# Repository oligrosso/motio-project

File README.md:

# 🧠 MOTIO — Biomedical Instrumentation Project

**MOTIO** is an end-to-end **biomedical instrumentation system** designed for the **analysis and treatment support of Parkinson’s Disease**, providing a **non-invasive, portable, and objective** approach to motor symptom monitoring.

The project integrates **wearable hardware**, **embedded firmware**, and an **intelligent analysis platform**, enabling both clinical and ambulatory use.

> 🩺 *Making motion science accessible.*

---

## 🎯 Project Objective

The main goal of MOTIO is to develop and validate a system capable of:

- 🧤 Delivering **vibrotactile therapeutic stimulation**
- 📟 Objectively measuring motor symptoms, especially tremor
- 📊 Processing and visualizing motion data through a clinical interface
- 📈 Complementing (not replacing) traditional clinical assessments (e.g. MDS-UPDRS)

---

## 🧩 System Architecture Overview

### 📁 Repository Structure

- 🧤 **MotioGlove/** — Wearable vibrotactile therapeutic device  
- 📟 **MotioSensor/** — Portable inertial measurement device (IMU)  
- 📊 **MotioMetrics/** — Motion analysis and visualization platform  

Each module can operate independently, but together they form a **complete ecosystem** for treatment, measurement, and analysis.

---

## 🧤 MotioGlove — Vibrotactile Therapeutic Glove

Wearable glove designed to apply **Vibrotactile Coordinated Reset (vCR)** stimulation to the fingertips.

### 🔬 Scientific Background
Based on research by **Tass et al. (Stanford University)**, vCR aims to **desynchronize pathological neural networks** using controlled mechanical stimulation.

### ⚙️ Key Features
- Vibrotactile stimulation at **250 Hz**
- Alternating stimulation of **finger pairs**
- Randomized stimulation sequences (**Fisher–Yates algorithm**)
- Temporal pauses with **jitter**
- Autonomous **2-hour therapy sessions**
- Button-based control and LED feedback

### ✅ Advantages
- Non-invasive
- Portable
- Ambulatory use
- High patient comfort
- No reported side effects

---

## 📟 MotioSensor — Inertial Measurement Device

Portable sensing unit designed to objectively capture motion data with **clinical-grade precision**.

### 🧠 Measured Signals
- 3-axis acceleration
- 3-axis angular velocity
- Orientation estimation (Yaw, Pitch, Roll)

### 🔄 Operating Modes
- 🏥 **Clinical mode**: real-time WiFi transmission
- 🏠 **Ambulatory mode**: local storage on microSD card

### 📁 Output
- `.csv` files containing:
  - Raw sensor signals
  - Timestamped activity annotations

---

## 📊 MotioMetrics — Motion Analysis Platform

Software platform responsible for **data processing, analysis, and visualization**.

### 🧠 Backend (Python)
- CSV file ingestion
- Automatic signal processing
- Tremor episode detection
- Computation of:
  - Dominant frequency
  - RMS amplitude
  - Episode duration
- Spectral analysis (FFT + **Burg method**)

### 🖥️ Web Interface
- Clinical-oriented UI
- Manual CSV upload
- Interactive visualizations (Plotly.js)
- Patient data registration
- PDF report export
- Local measurement history

### 🔴 Real-Time Analysis
- **WebSocket-based** communication
- Live signal visualization
- Activity logging with timestamps
- Automatic download of recorded data at session end

---

## 🔁 System Workflow

### 🧪 Real-Time Analysis
```mermaid
flowchart LR
  A[MotioSensor] -->|WiFi / WebSockets| B[MotioMetrics backend]
  B --> C[Live processing]
  C --> D[Web interface]
  D --> E[Live visualization]
```

### 📂 Offline CSV Analysis

```mermaid
flowchart LR
  A[MotioSensor<br/>CSV files] --> B[MotioMetrics]
  B --> C[Signal processing]
  C --> D[Metrics extraction]
  D --> E[Reports and visualizations]
```
## 🧪 Validation & Results

The system was evaluated on:
- Parkinson’s patients with tremor
- Parkinson’s patients without tremor (dyskinesia)
- Control subjects

Results demonstrated:
- Strong correlation with clinical evaluation
- Robust tremor episode detection
- High usability and acceptance by patients and clinicians

---

## 🛠️ Technologies Used

- **Python** (signal processing & backend)
- **Flask + Socket.IO**
- **JavaScript / HTML / CSS**
- **Plotly.js**
- **ESP8266 (Wemos D1 Mini)**
- **MPU6050 IMU**
- **Render + GitHub**

---

## 👩‍🔬 Team

Developed as part of  
**Biomedical Instrumentation II — ITBA**

**Group 1**
- Alexa Sessarego Aurich
- Jazmín Azul Fermani  
- Olivia Grosso  
---

## ⚠️ Disclaimer

This project was developed for **academic and research purposes only**.  
It is **not a certified medical device** for commercial clinical use.

## 🗂️ Module Interaction Diagram
```mermaid
flowchart LR

  subgraph Wearables
    G[MotioGlove<br/>Vibrotactile therapy]
    P[Patient]
    S[MotioSensor<br/>IMU data acquisition]
    G -->|Therapy| P -->|Motion| S
  end

  subgraph Software
    B[MotioMetrics backend]
    W[Web interface]
    D[Desktop application]
    B --> W
    B --> D
  end

  S -->|Motion data| B

```

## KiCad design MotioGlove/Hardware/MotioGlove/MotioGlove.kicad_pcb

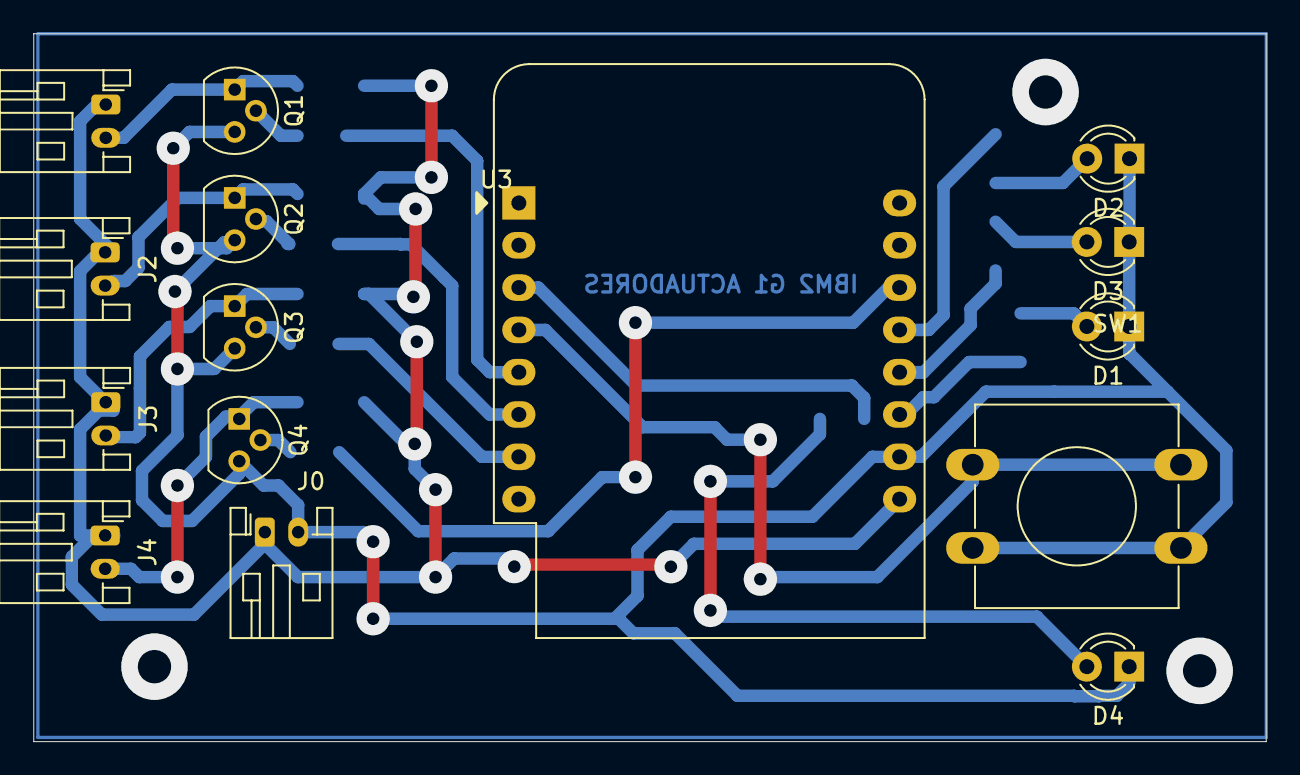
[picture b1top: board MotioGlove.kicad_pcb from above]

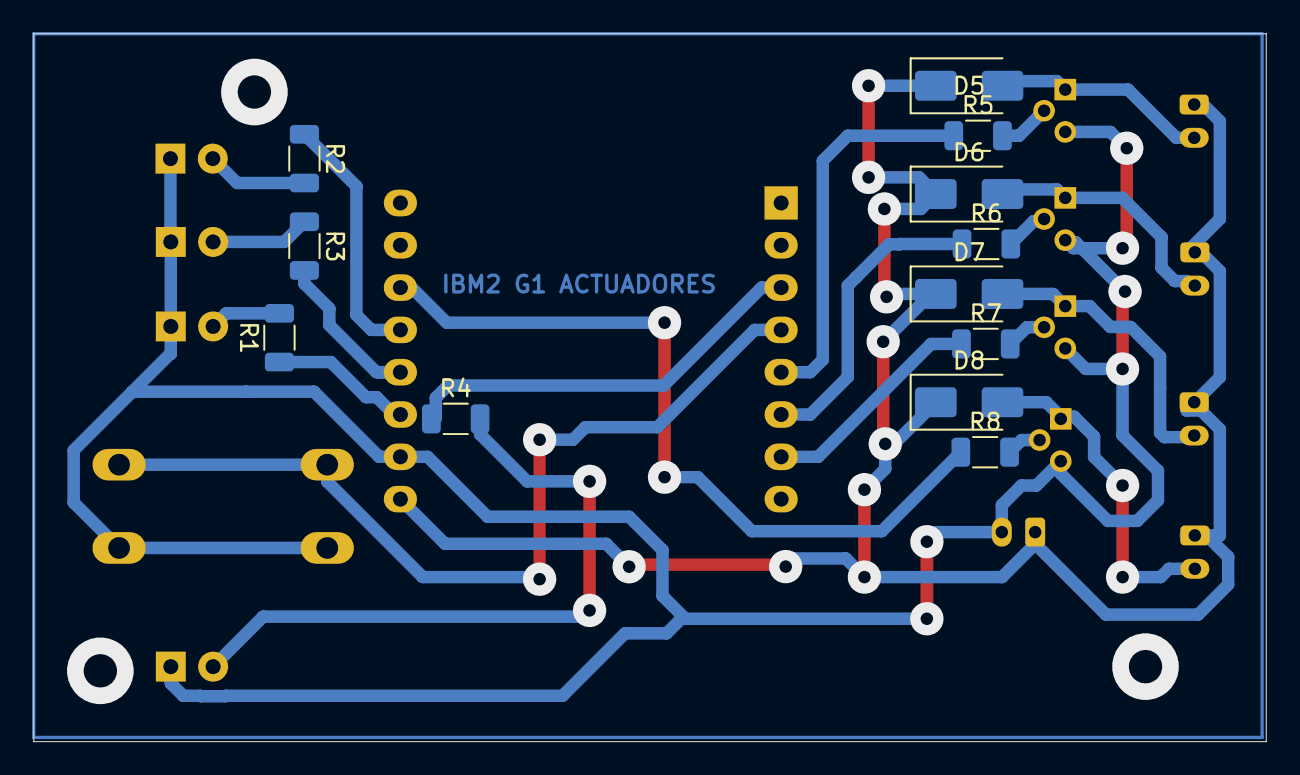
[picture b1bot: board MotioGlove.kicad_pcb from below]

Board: 2 copper layers, 74.0 x 42.5 mm, 27 parts (12 on the bottom side), 23 nets.

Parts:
D1, D2, D3: LED; LED_D3.0mm
D4: LED_STATUS; LED_D3.0mm
D5, D6, D7, D8: D; D_SMA
J0: 5V; JST_PH_S2B-PH-K_1x02_P2.00mm_Horizontal
J1, J2, J3, J4: Conn_01x02; JST_PH_S2B-PH-K_1x02_P2.00mm_Horizontal
Q1, Q2, Q3, Q4: BC547; TO-92
R1, R2, R3, R4, R5, R6, R7, R8: R; R_1206_3216Metric
SW1: SW_Push; SW_PUSH-12mm
U3: WEMOS_D1_mini; WEMOS_D1_mini_light

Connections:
/5V: D5.1 (K), D6.1 (K), D7.1 (K), D8.1 (K), J0.1, J1.1, J2.1, J3.1, J4.1, U3.9 (5V)
/D0: R4.1, U3.3 (D0)
/D1: R8.1, U3.14 (SCL/D1)
/D2: R2.1, U3.13 (SDA/D2)
/D3: R3.2, U3.12 (D3)
/D4: R1.1, U3.11 (D4)
/D5: SW1.1, U3.4 (SCK/D5)
/D6: R5.1, U3.5 (MISO/D6)
/D7: R6.1, U3.6 (MOSI/D7)
/D8: R7.1, U3.7 (CS/D8)
/GND: D1.1 (K), D2.1 (K), D3.1 (K), D4.1 (K), J0.2, Q1.3 (E), Q2.3 (E), Q3.3 (E), Q4.3 (E), SW1.2, U3.10 (GND)
unnamed: D1.2 (A), R1.2
unnamed: D2.2 (A), R2.2
unnamed: D3.2 (A), R3.1
unnamed: D4.2 (A), R4.2
unnamed: D5.2 (A), J1.2, Q1.1 (C)
unnamed: D6.2 (A), J2.2, Q2.1 (C)
unnamed: D7.2 (A), J3.2, Q3.1 (C)
unnamed: D8.2 (A), J4.2, Q4.1 (C)
unnamed: Q1.2 (B), R5.2
unnamed: Q2.2 (B), R6.2
unnamed: Q3.2 (B), R7.2
unnamed: Q4.2 (B), R8.2

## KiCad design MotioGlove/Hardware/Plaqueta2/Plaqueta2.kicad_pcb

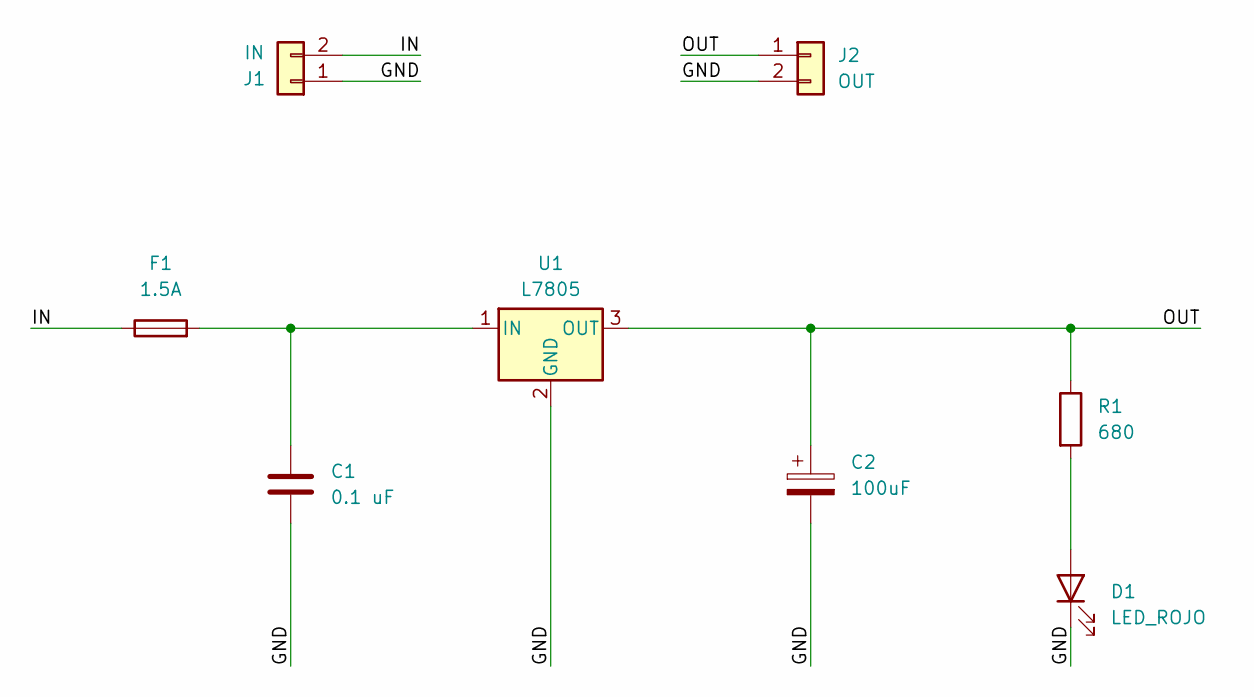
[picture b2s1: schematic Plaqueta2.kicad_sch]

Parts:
C1: 0.1 uF; C_Disc_D5.0mm_W2.5mm_P2.50mm
C2: 100uF; CP_Radial_D5.0mm_P2.50mm
D1: LED_ROJO; LED_0805_2012Metric
F1: 1.5A; Fuseholder_Cylinder-5x20mm_Schurter_0031_8201_Horizontal_Op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
J1: IN; PinHeader_1x02_P2.54mm_Vertical
J2: OUT; PinHeader_1x02_P2.54mm_Vertical
R1: 680; R_1206_3216Metric
U1: L7805; TO-252-2

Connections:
/GND: C1.2, C2.2, D1.1 (K), J1.1, J2.2, U1.2 (GND)
/IN: F1.1, J1.2
/OUT: C2.1, J2.1, R1.1, U1.3 (OUT)
unnamed: D1.2 (A), R1.2
unnamed: C1.1, F1.2, U1.1 (IN)

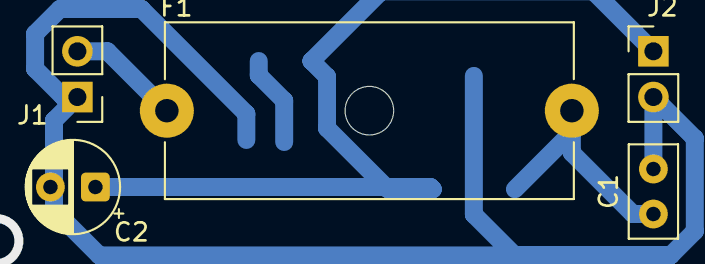
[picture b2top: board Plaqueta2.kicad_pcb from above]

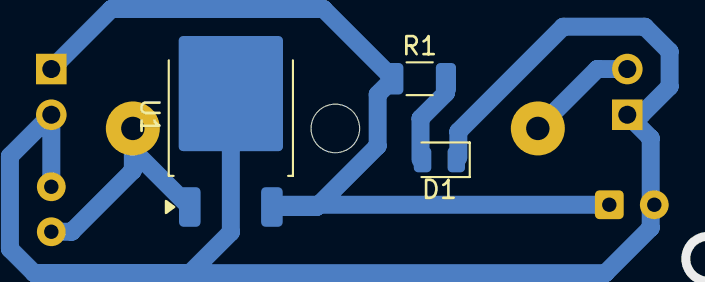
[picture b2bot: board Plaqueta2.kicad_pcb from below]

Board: 2 copper layers, 8 parts (3 on the bottom side), 5 nets.

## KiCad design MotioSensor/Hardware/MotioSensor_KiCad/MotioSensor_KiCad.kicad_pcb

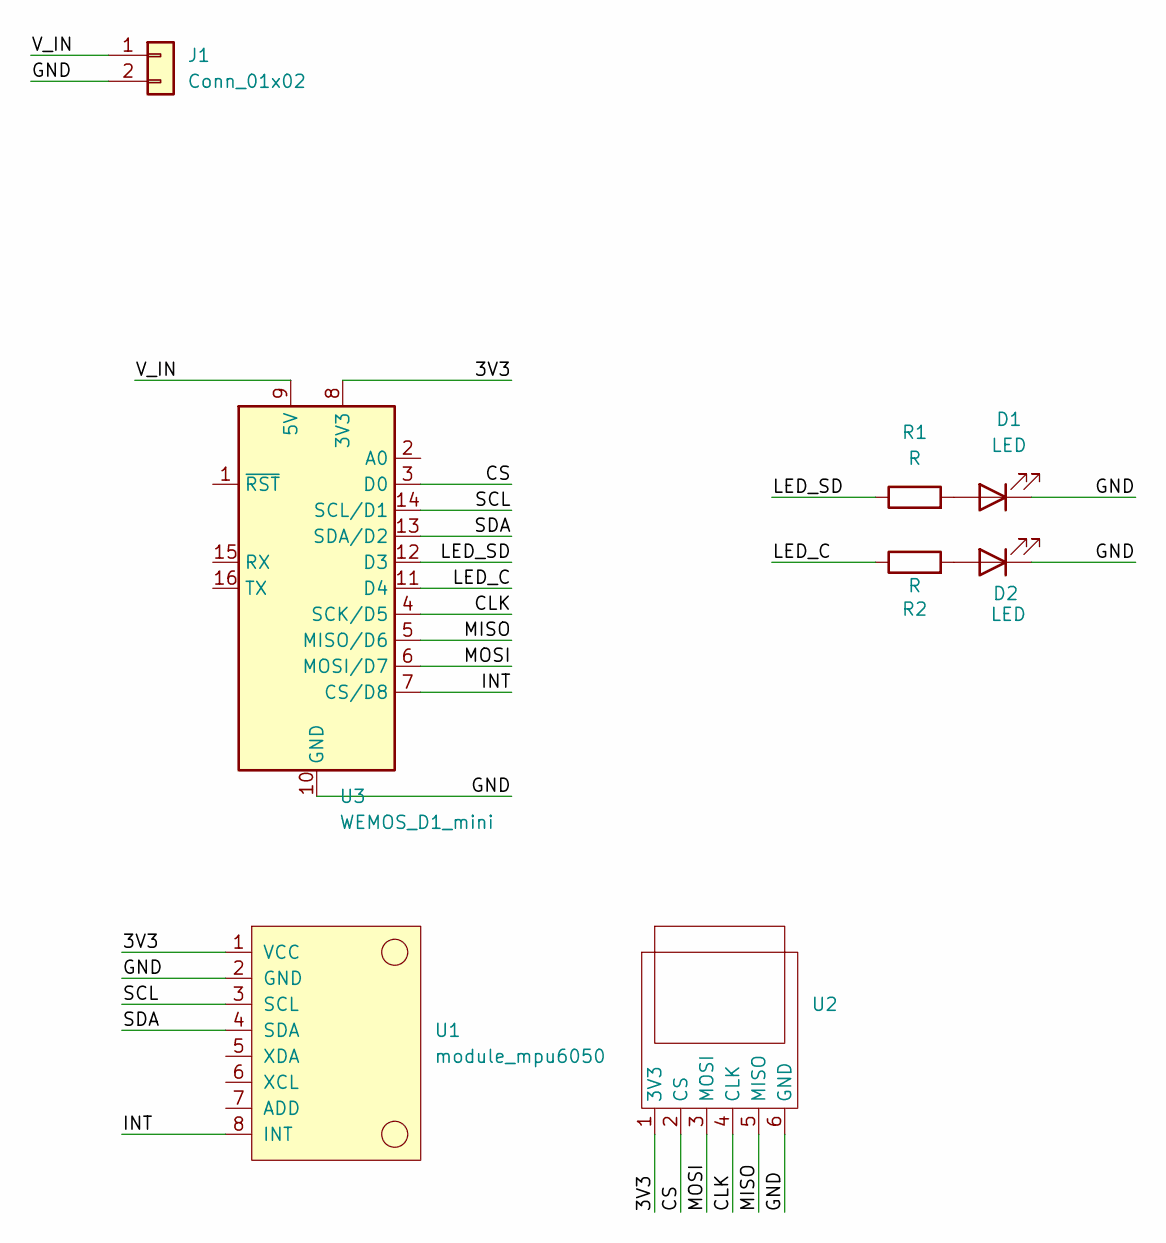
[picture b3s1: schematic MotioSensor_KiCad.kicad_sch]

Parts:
D1, D2: LED; LED_D5.0mm
J1: Conn_01x02; PinHeader_1x02_P2.54mm_Vertical
R1, R2: R; R_1206_3216Metric
U1: module_mpu6050
U2: PinHeader_1x06_P2.54mm_Vertical
U3: WEMOS_D1_mini; WEMOS_D1_mini_light

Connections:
/3V3: U1.1 (VCC), U2.1 (3V3), U3.8 (3V3)
/CLK: U2.4 (CLK), U3.4 (SCK/D5)
/CS: U2.2 (CS), U3.3 (D0)
/GND: D1.1 (K), D2.1 (K), J1.2, U1.2 (GND), U2.6 (GND), U3.10 (GND)
/INT: U1.8 (INT), U3.7 (CS/D8)
/LED_C: R2.1, U3.11 (D4)
/LED_SD: R1.1, U3.12 (D3)
/MISO: U2.5 (MISO), U3.5 (MISO/D6)
/MOSI: U2.3 (MOSI), U3.6 (MOSI/D7)
/SCL: U1.3 (SCL), U3.14 (SCL/D1)
/SDA: U1.4 (SDA), U3.13 (SDA/D2)
/V_IN: J1.1, U3.9 (5V)
unnamed: D1.2 (A), R1.2
unnamed: D2.2 (A), R2.2

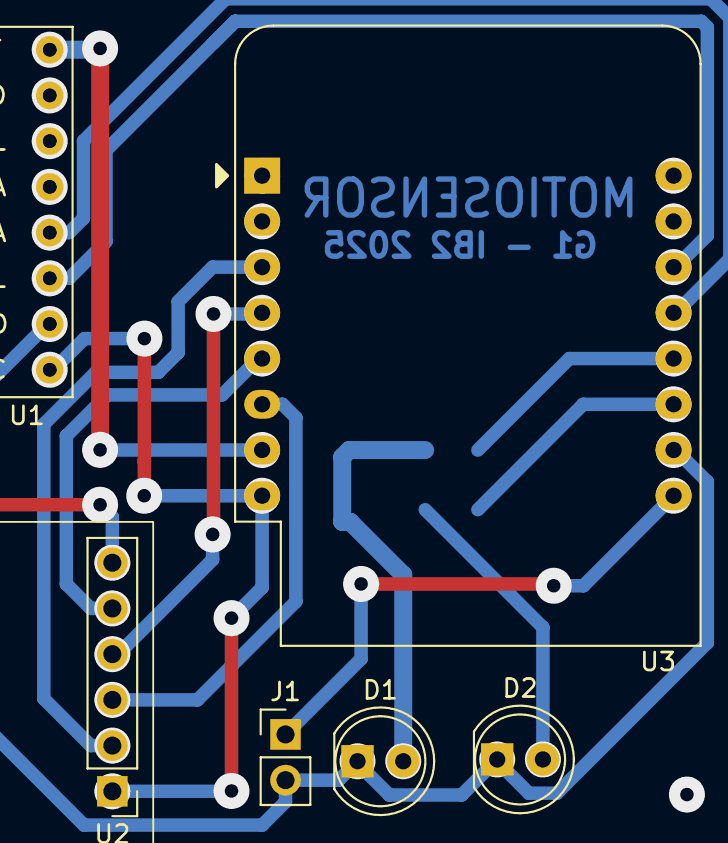
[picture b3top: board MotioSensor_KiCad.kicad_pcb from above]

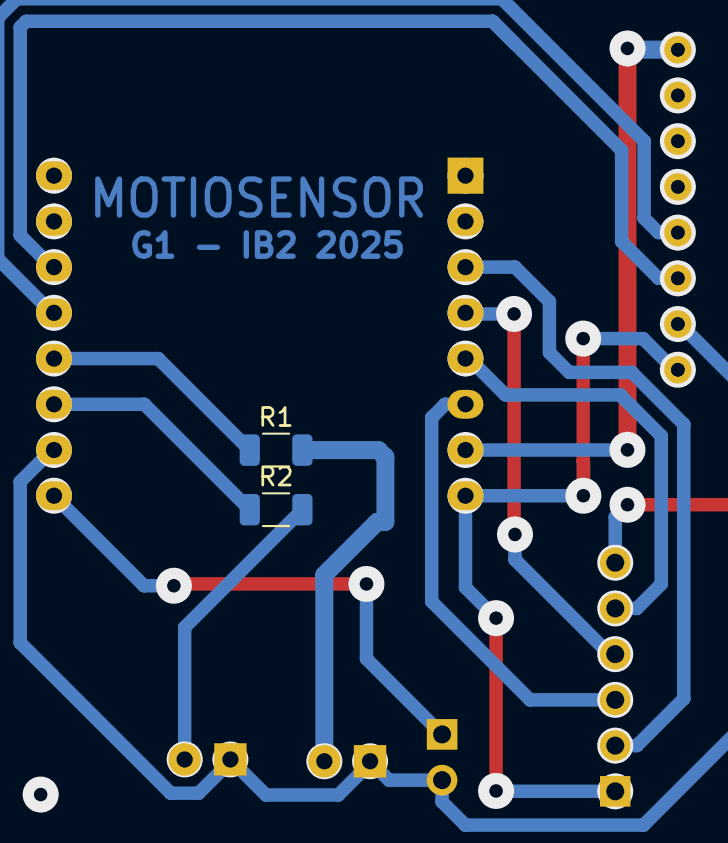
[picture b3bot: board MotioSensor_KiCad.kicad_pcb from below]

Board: 2 copper layers, 8 parts (2 on the bottom side), 14 nets.

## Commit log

2025-12-01 Carga inicial: Estructura del proyecto MotioSystem
2025-12-01 Chore: Actualizar archivos rastreados
2025-12-01 Limpieza profunda: Aplicando gitignore nuevo
2025-12-20 Reorganizacion de la estructura del repositorio
2025-12-20 Reorganizacion del repositorio
2025-12-21 Modificacion de analisis de datos
2025-12-23 Actualización MotioGlove y Websockets
2026-01-10 Add MotioMetrics module and project gitignore
2026-01-10 Convert MotioMetrics from nested repo to regular folder
2026-01-10 Move legacy HTTP backend and utility scripts to archive/tools
2026-01-10 Organize desktop app files and track PyInstaller spec
2026-01-10 Fix asset paths after moving logos to web/assets
2026-01-10 Create README.md
    Add comprehensive project README with system overview and diagrams
2026-01-16 Add frontend to docs for Github Pages
2026-01-16 Message change in live analisis of MotioSensor's data
2026-01-16 Update connection prompt text
